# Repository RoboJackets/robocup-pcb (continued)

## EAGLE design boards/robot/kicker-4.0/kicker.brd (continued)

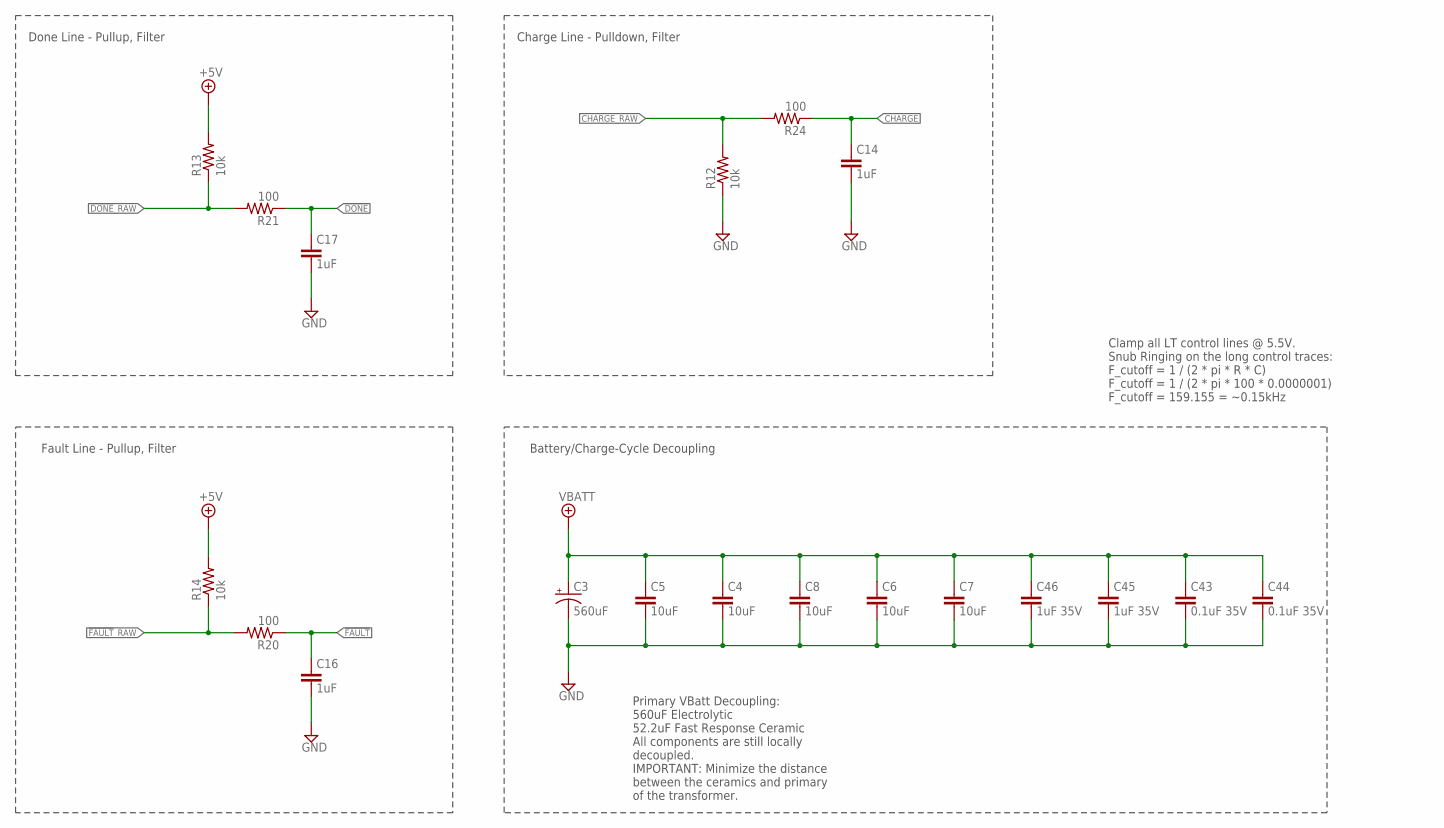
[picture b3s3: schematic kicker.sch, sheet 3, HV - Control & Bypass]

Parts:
C3: 560uF; E7,5-18
C4, C5, C6, C7, C8: 10uF; C1210
C14, C16, C17: 1uF; C0603
C43, C44: 0.1uF 35V; C0805
C45, C46: 1uF 35V; C0805
R12, R13, R14: 10k; R0603
R20, R21, R24: 100; R0603

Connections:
!DONE!: C17.1, R21.1; also elsewhere on the board
!DONE!_RAW: R13.1, R21.2; also elsewhere on the board
!FAULT!: C16.1, R20.1; also elsewhere on the board
!FAULT!_RAW: R14.1, R20.2; also elsewhere on the board
+5V: R13.2, R14.2; also elsewhere on the board
CHARGE: C14.1, R24.1; also elsewhere on the board
CHARGE_RAW: R12.2, R24.2; also elsewhere on the board
GND: C3.-, C4.2, C5.2, C6.2, C7.2, C8.2, C14.2, C16.2, C17.2, C43.2, C44.2, C45.2, C46.2, R12.1; also elsewhere on the board
VBATT: C3.+, C4.1, C5.1, C6.1, C7.1, C8.1, C43.1, C44.1, C45.1, C46.1; also elsewhere on the board

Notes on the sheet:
Done Line - Pullup, Filter
Fault Line - Pullup, Filter
Charge Line - Pulldown, Filter
Battery/Charge-Cycle Decoupling
Clamp all LT control lines @ 5.5V. Snub Ringing on the long control traces: F_cutoff = 1 / (2 * pi * R * C) F_cutoff = 1 / (2 * pi * 100 * 0.0000001) F_cutoff = 159.155 = ~0.15kHz
Primary VBatt Decoupling: 560uF Electrolytic 52.2uF Fast Response Ceramic All components are still locally decoupled. IMPORTANT: Minimize the distance between the ceramics and primary of the transformer.

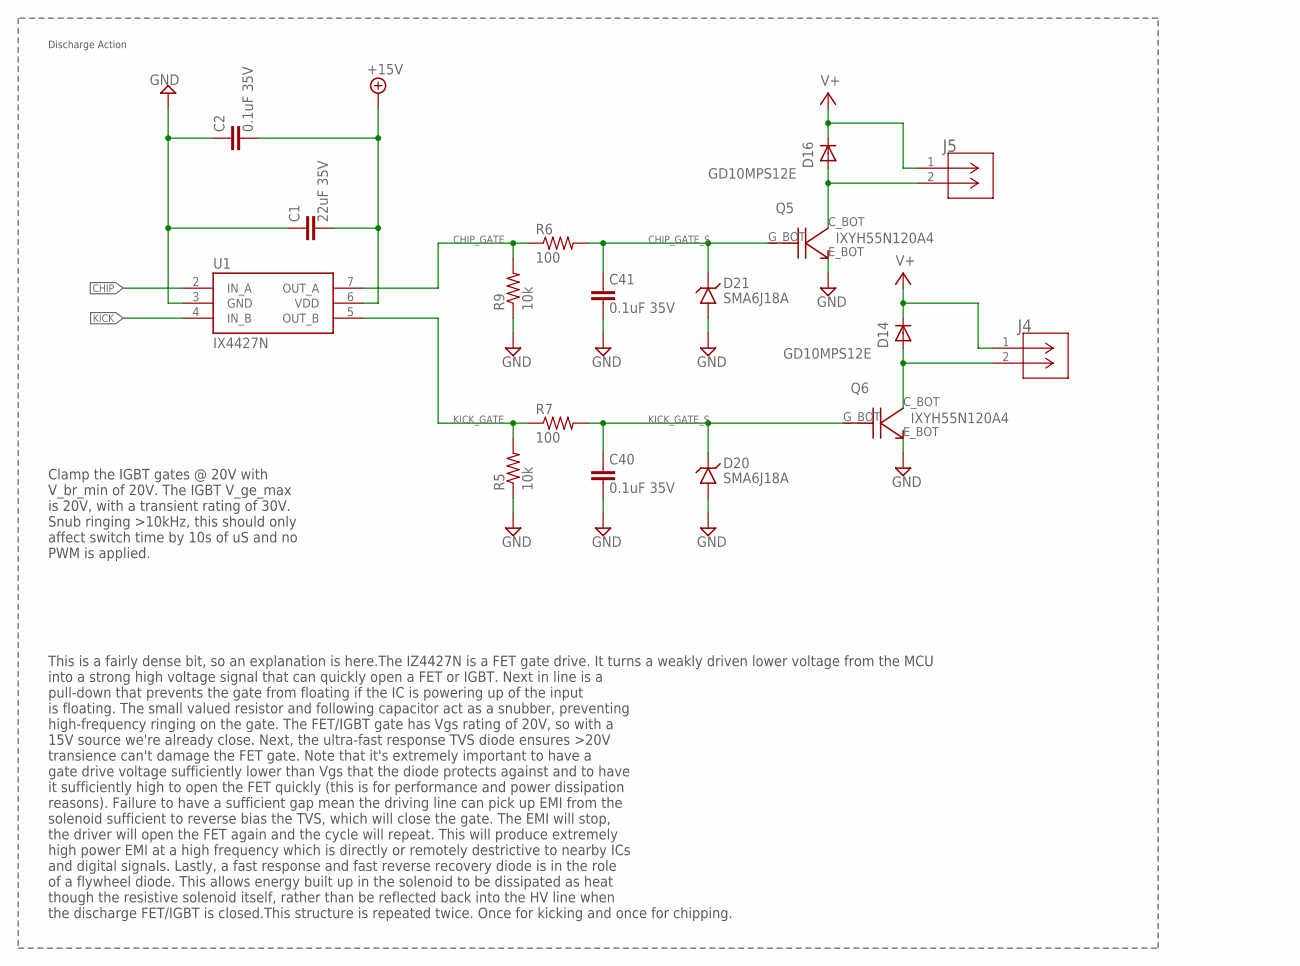
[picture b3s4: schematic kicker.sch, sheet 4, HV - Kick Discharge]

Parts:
C1: 22uF 35V; C0805
C2: 0.1uF 35V; C0805
C40, C41: 0.1uF 35V; C0603
D14, D16: GD10MPS12E; TO460P990X239-3
D20, D21: SMA6J18A; RESM5226X262
J4, J5: 436500202; CON_436500202_MOL
Q5, Q6: IXYH55N120A4; TO264
R5, R9: 10k; R0603
R6, R7: 100; R1206
U1: IX4427N; SOIC-8

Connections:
+15V: C1.2, C2.2, U1.6 (VDD); also elsewhere on the board
CHIP: U1.2 (IN_A); also elsewhere on the board
CHIPPER: D16.2 (A), J5.2, Q5.C_BOT (C)
CHIP_GATE: R6.1, R9.2, U1.7 (OUT_A)
CHIP_GATE_S: C41.1, D21.2 (C), Q5.G_BOT (G), R6.2
GND: C1.1, C2.1, C40.2, C41.2, D20.1 (A), D21.1 (A), Q5.E_BOT (E), Q6.E_BOT (E), R5.1, R9.1, U1.3 (GND); also elsewhere on the board
KICK: U1.4 (IN_B); also elsewhere on the board
KICKER: D14.2 (A), J4.2, Q6.C_BOT (C)
KICK_GATE: R5.2, R7.1, U1.5 (OUT_B)
KICK_GATE_S: C40.1, D20.2 (C), Q6.G_BOT (G), R7.2
V+: D14.3 (C), D16.3 (C), J4.1, J5.1; also elsewhere on the board

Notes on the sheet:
Discharge Action
Clamp the IGBT gates @ 20V with V_br_min of 20V. The IGBT V_ge_max is 20V, with a transient rating of 30V. Snub ringing >10kHz, this should only affect switch time by 10s of uS and no PWM is applied.
This is a fairly dense bit, so an explanation is here.The IZ4427N is a FET gate drive. It turns a weakly driven lower voltage from the MCU into a strong high voltage signal that can quickly open a FET or IGBT. Next in line is a pull-down that prevents the gate from floating if the IC is powering up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

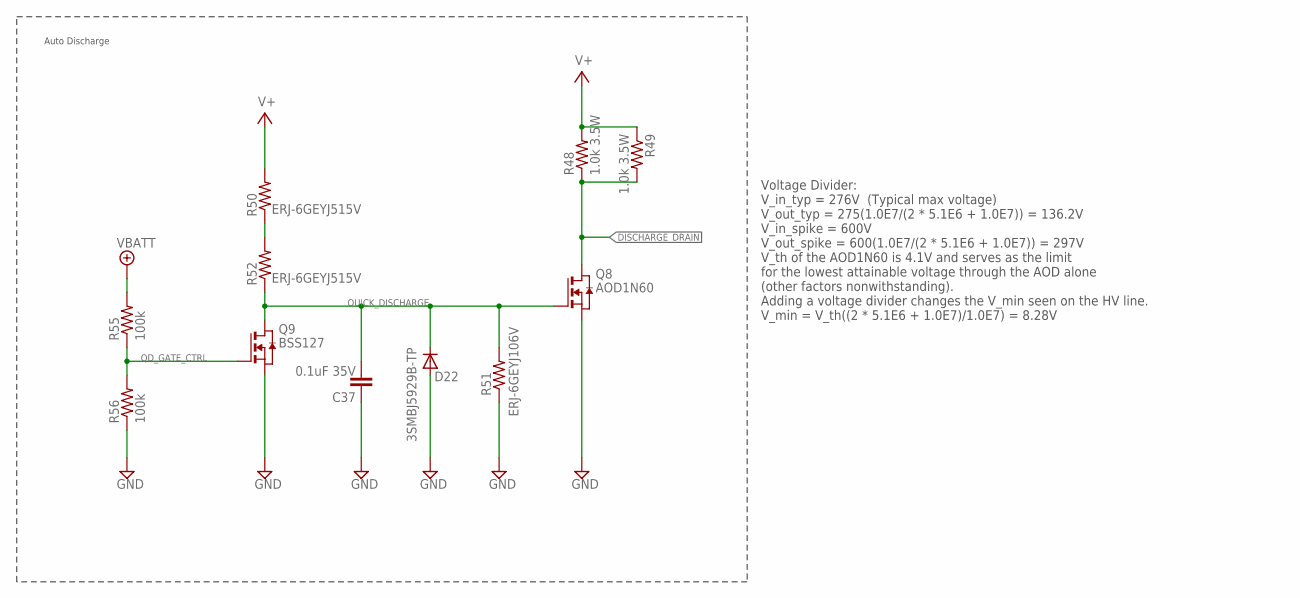
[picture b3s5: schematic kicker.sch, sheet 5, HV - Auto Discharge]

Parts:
C37: 0.1uF 35V; C0603
D22: 3SMBJ5929B-TP; DO214AA
Q8: AOD1N60; DPAK
Q9: BSS127; SOT-23-3
R48, R49: 1.0k 3.5W; TO508P1539X450-3; DIGIKEY PWR263S-35-1501F
R50, R52: ERJ-6GEYJ515V; R0805
R51: ERJ-6GEYJ106V; R0603
R55, R56: 100k; R0603

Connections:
DISCHARGE_DRAIN: Q8.4 (D), R48.1 (PIN1), R49.2 (PIN2); also elsewhere on the board
GND: C37.1, D22.A, Q8.3 (S), Q9.2 (S), R51.1, R56.1; also elsewhere on the board
QD_GATE_CTRL: Q9.1 (G), R55.1, R56.2
QD_PU_BR: R50.1, R52.2
QUICK_DISCHARGE: C37.2, D22.C, Q8.1 (G), Q9.3 (D), R51.2, R52.1
V+: R48.2 (PIN2), R49.1 (PIN1), R50.2; also elsewhere on the board
VBATT: R55.2; also elsewhere on the board

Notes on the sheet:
Auto Discharge
Voltage Divider: V_in_typ = 276V (Typical max voltage) V_out_typ = 275(1.0E7/(2 * 5.1E6 + 1.0E7)) = 136.2V V_in_spike = 600V V_out_spike = 600(1.0E7/(2 * 5.1E6 + 1.0E7)) = 297V V_th of the AOD1N60 is 4.1V and serves as the limit for the lowest attainable voltage through the AOD alone (other factors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

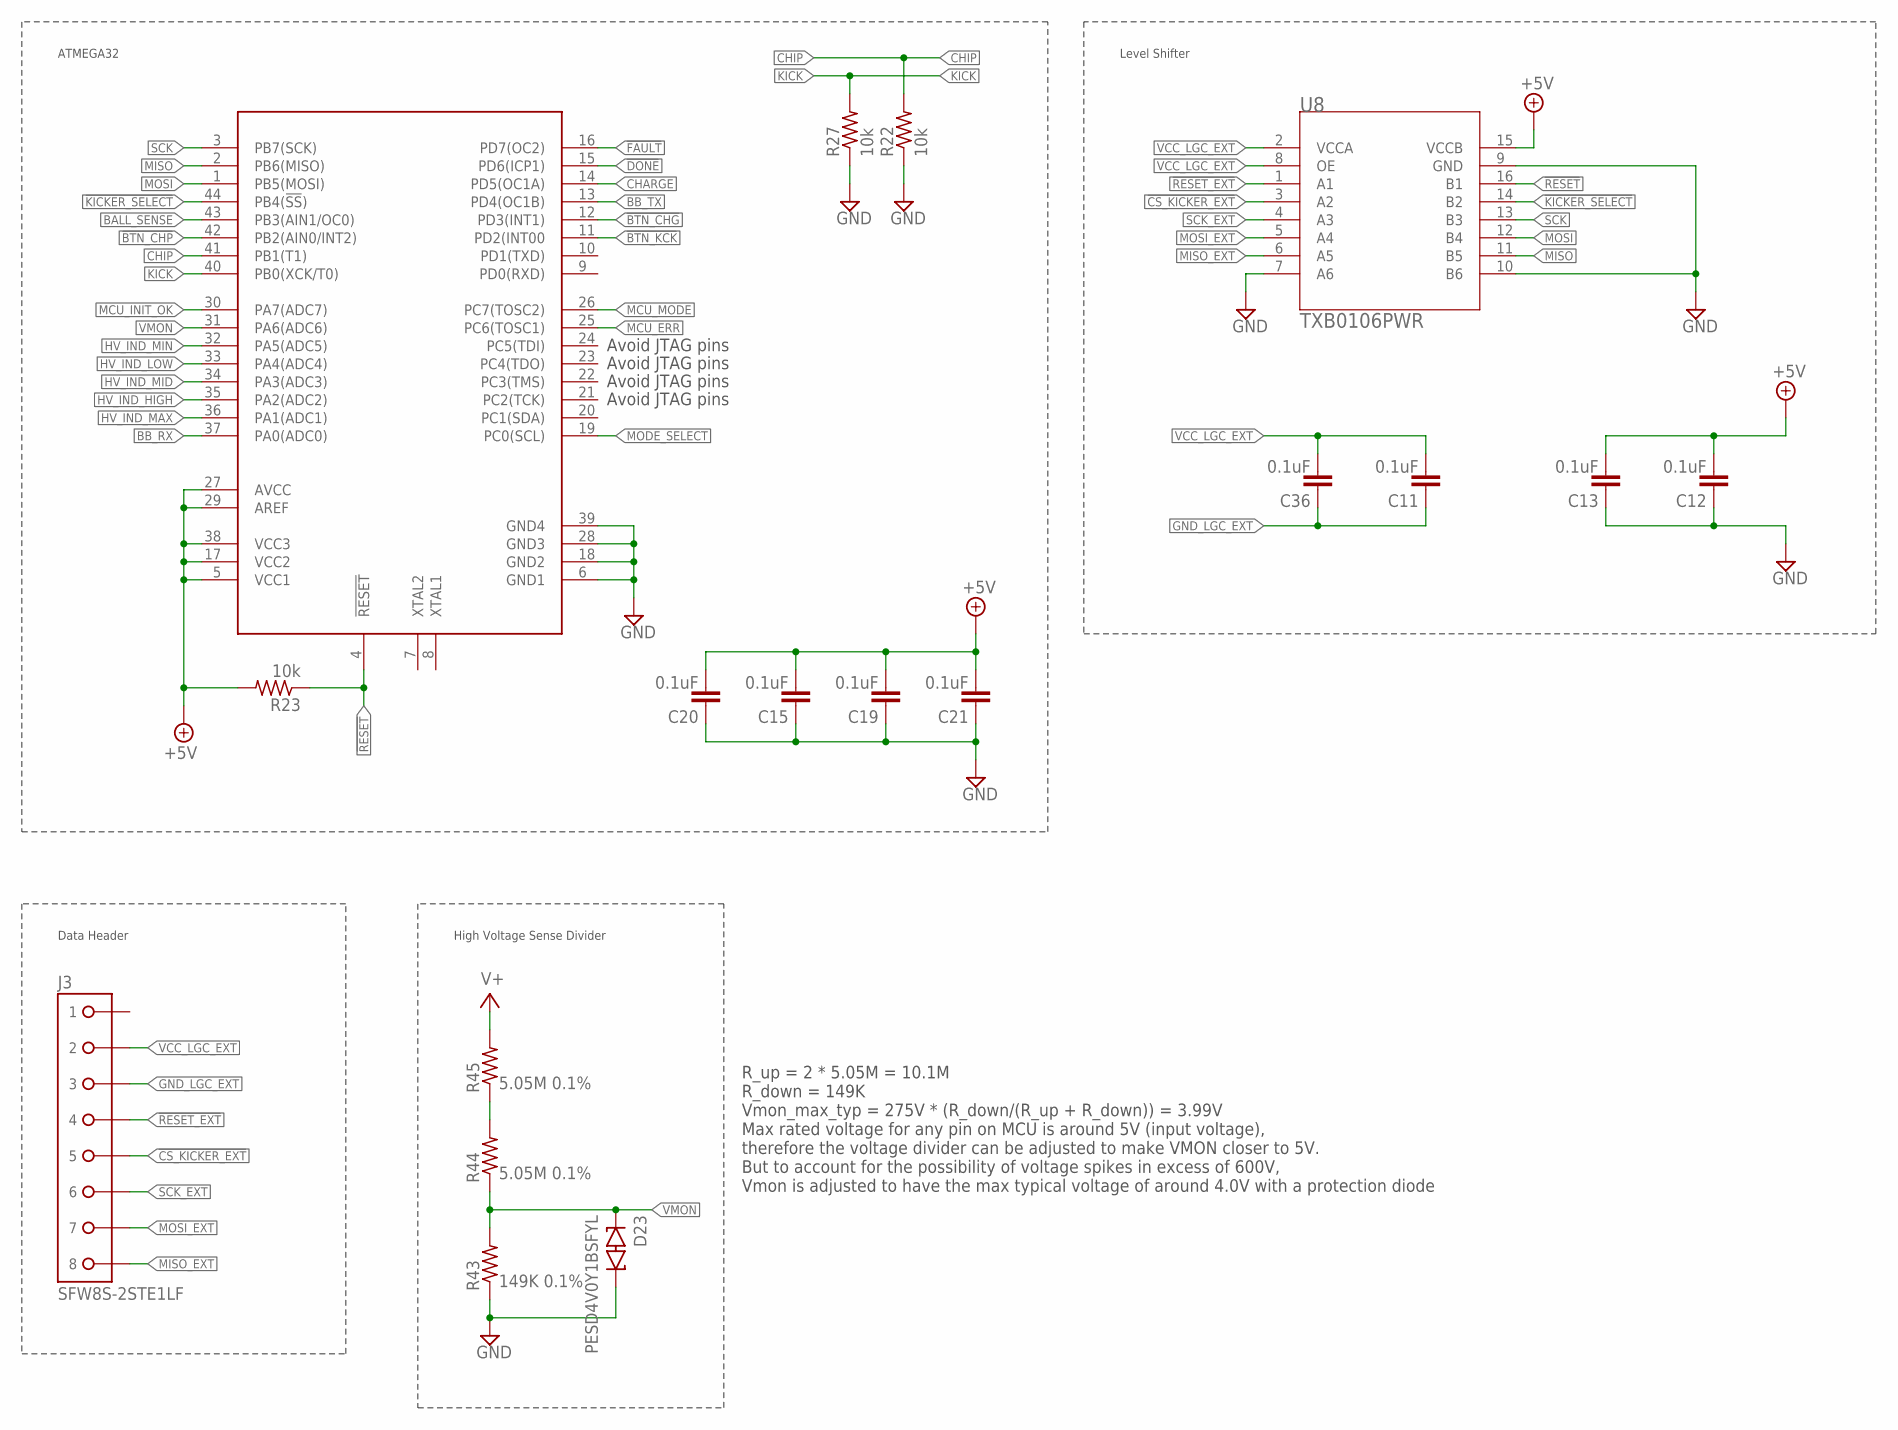
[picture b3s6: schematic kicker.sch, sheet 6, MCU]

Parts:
C11, C12, C13, C15, C19, C20, C21, C36: 0.1uF; C0603
D23: PESD4V0Y1BSFYL; DSN0603-2
J3: SFW8S-2STE1LF; CON8_1X8_UB_SFW_JAE
R22, R23, R27: 10k; R0603
R43: 149K 0.1%; R0603
R44, R45: 5.05M 0.1%; R0805
U5: AT32ATQFP44; QFP80P1200X1200X120-44
U8: TXB0106PWR; PW16

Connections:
!BTN_CHG: U5.12 (PD3(INT1)); also elsewhere on the board
!BTN_CHP: U5.42 (PB2(AIN0/INT2)); also elsewhere on the board
!BTN_KCK: U5.11 (PD2(INT00); also elsewhere on the board
!CS_KICKER_EXT: J3.5, U8.3 (A2)
!DONE!: U5.15 (PD6(ICP1)); also elsewhere on the board
!FAULT!: U5.16 (PD7(OC2)); also elsewhere on the board
!KICKER_SELECT: U5.44 (PB4(!SS!)), U8.14 (B2)
!RESET: R23.1, U5.4 (!RESET!), U8.16 (B1)
!RESET_EXT: J3.4, U8.1 (A1)
+5V: C12.2, C13.2, C15.2, C19.2, C20.2, C21.2, R23.2, U5.5 (VCC1), U5.17 (VCC2), U5.27 (AVCC), U5.29 (AREF), U5.38 (VCC3), U8.15 (VCCB); also elsewhere on the board
BALL_SENSE: U5.43 (PB3(AIN1/OC0)); also elsewhere on the board
BB_RX: U5.37 (PA0(ADC0)); also elsewhere on the board
BB_TX: U5.13 (PD4(OC1B)); also elsewhere on the board
CHARGE: U5.14 (PD5(OC1A)); also elsewhere on the board
CHIP: R22.2, U5.41 (PB1(T1)); also elsewhere on the board
GND: C12.1, C13.1, C15.1, C19.1, C20.1, C21.1, D23.C2, R22.1, R27.1, R43.1, U5.6 (GND1), U5.18 (GND2), U5.28 (GND3), U5.39 (GND4), U8.7 (A6), U8.9 (GND), U8.10 (B6); also elsewhere on the board
GND_LGC_EXT: C11.1, C36.1, J3.3
HV_IND_HIGH: U5.35 (PA2(ADC2)); also elsewhere on the board
HV_IND_LOW: U5.33 (PA4(ADC4)); also elsewhere on the board
HV_IND_MAX: U5.36 (PA1(ADC1)); also elsewhere on the board
HV_IND_MID: U5.34 (PA3(ADC3)); also elsewhere on the board
HV_IND_MIN: U5.32 (PA5(ADC5)); also elsewhere on the board
HV_SENSE_DIV_BR: R44.2, R45.1
KICK: R27.2, U5.40 (PB0(XCK/T0)); also elsewhere on the board
MCU_ERR: U5.25 (PC6(TOSC1)); also elsewhere on the board
MCU_INIT_OK: U5.30 (PA7(ADC7)); also elsewhere on the board
MCU_MODE: U5.26 (PC7(TOSC2)); also elsewhere on the board
MISO: U5.2 (PB6(MISO)), U8.11 (B5)
MISO_EXT: J3.8, U8.6 (A5)
MODE_SELECT: U5.19 (PC0(SCL)); also elsewhere on the board
MOSI: U5.1 (PB5(MOSI)), U8.12 (B4)
MOSI_EXT: J3.7, U8.5 (A4)
SCK: U5.3 (PB7(SCK)), U8.13 (B3)
SCK_EXT: J3.6, U8.4 (A3)
V+: R45.2; also elsewhere on the board
VCC_LGC_EXT: C11.2, C36.2, J3.2, U8.2 (VCCA), U8.8 (OE)
VMON: D23.C1, R43.2, R44.1, U5.31 (PA6(ADC6))

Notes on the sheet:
ATMEGA32
Data Header
High Voltage Sense Divider
Avoid JTAG pins
R_up = 2 * 5.05M = 10.1M R_down = 149K Vmon_max_typ = 275V * (R_down/(R_up + R_down)) = 3.99V Max rated voltage for any pin on MCU is around 5V (input voltage), therefore the voltage divider can be adjusted to make VMON closer to 5V. But to account for the possibility of voltage spikes in excess of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
Level Shifter

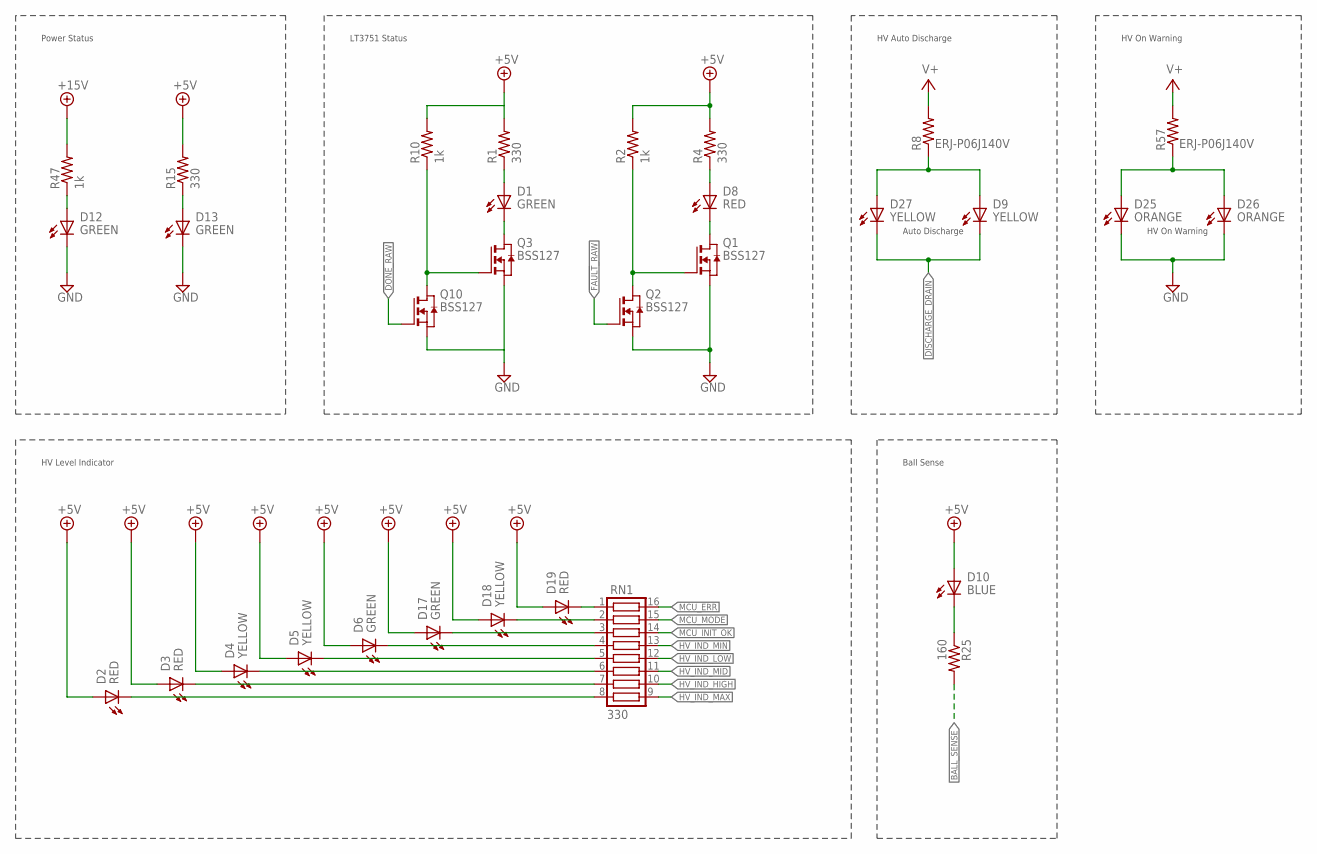
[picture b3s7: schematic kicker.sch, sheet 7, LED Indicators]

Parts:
D1, D6, D12, D13, D17: GREEN; CHIP-LED0603
D2, D3, D8, D19: RED; CHIP-LED0603
D4, D5, D9, D18, D27: YELLOW; CHIP-LED0603
D10: BLUE; CHIP-LED0603
D25, D26: ORANGE; CHIP-LED0603; MPN LTST-C191KFKT; DIGIKEY 160-1445-1-ND
Q1, Q2, Q3, Q10: BSS127; SOT-23-3
R1, R4, R15: 330; R0603
R2, R10, R47: 1k; R0603
R8, R57: ERJ-P06J140V; R0805
R25: 160; R0603
RN1: 330; RA-8_2506

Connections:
15V_PWR_BR: D12.A, R47.1
!DONE!_RAW: Q10.1 (G); also elsewhere on the board
!FAULT!_RAW: Q2.1 (G); also elsewhere on the board
+5V: D2.A, D3.A, D4.A, D5.A, D6.A, D10.A, D17.A, D18.A, D19.A, R1.2, R2.2, R4.2, R10.2, R15.2; also elsewhere on the board
+15V: R47.2; also elsewhere on the board
BALL_SENSE: R25.2; also elsewhere on the board
BALL_SENSE_CL: D10.C (K), R25.1
DISCHARGE_DRAIN: D9.C (K), D27.C (K); also elsewhere on the board
FAULT_INV_BR: Q1.1 (G), Q2.3 (D), R2.1
FAULT_INV_BR1: Q3.1 (G), Q10.3 (D), R10.1
GND: D12.C (K), D13.C (K), D25.C (K), D26.C (K), Q1.2 (S), Q2.2 (S), Q3.2 (S); also elsewhere on the board
GND1: Q10.2 (S)
HV_IND_HIGH: RN1.10; also elsewhere on the board
HV_IND_HIGH_CL: D3.C (K), RN1.7
HV_IND_LOW: RN1.12; also elsewhere on the board
HV_IND_LOW_CL: D5.C (K), RN1.5
HV_IND_MAX: RN1.9; also elsewhere on the board
HV_IND_MAX_CL: D2.C (K), RN1.8
HV_IND_MID: RN1.11; also elsewhere on the board
HV_IND_MID_CL: D4.C (K), RN1.6
HV_IND_MIN: RN1.13; also elsewhere on the board
HV_IND_MIN_CL: D6.C (K), RN1.4
MCU_ERR: RN1.16; also elsewhere on the board
MCU_ERR_CL: D19.C (K), RN1.1
MCU_INIT_OK: RN1.14; also elsewhere on the board
MCU_INIT_OK_CL: D17.C (K), RN1.3
MCU_MODE: RN1.15; also elsewhere on the board
MCU_MODE_CL: D18.C (K), RN1.2
unnamed: D25.A, D26.A, R57.1
unnamed: D1.A, R1.1
unnamed: D13.A, R15.1
unnamed: D8.A, R4.1
unnamed: D8.C (K), Q1.3 (D)
unnamed: D9.A, D27.A, R8.1
unnamed: D1.C (K), Q3.3 (D)
V+: R8.2, R57.2; also elsewhere on the board

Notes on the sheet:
Power Status
LT3751 Status
Auto Discharge
HV Auto Discharge
HV Level Indicator
Ball Sense
HV On Warning

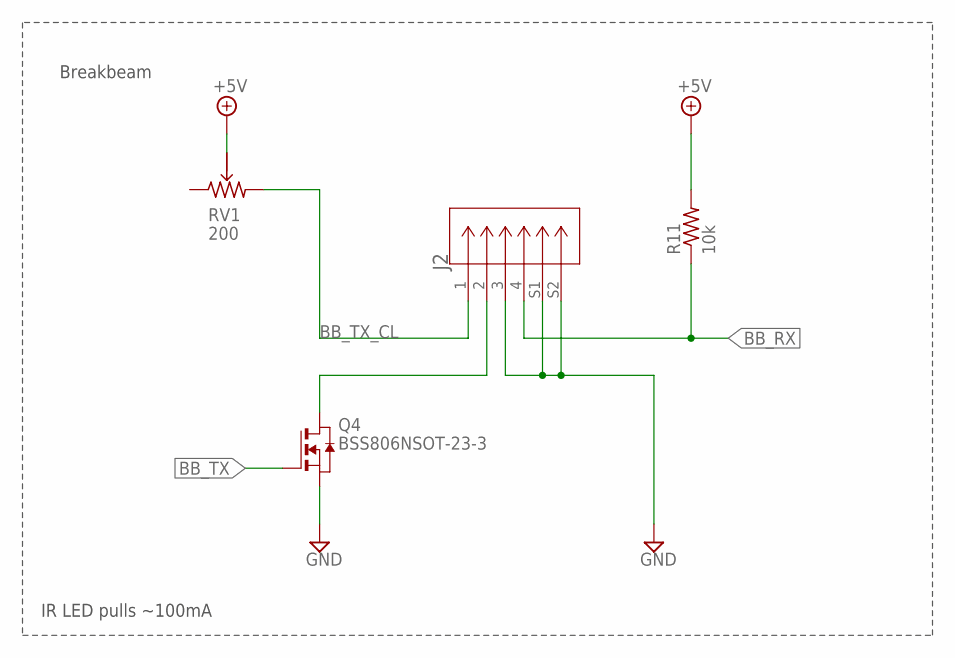
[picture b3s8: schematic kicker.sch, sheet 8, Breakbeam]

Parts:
J2: 430450411; CON_430450411_MOL
Q4: BSS806NSOT-23-3; SOT95P240X110-3
R11: 10k; R0603
RV1: 200; 3214J

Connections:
+5V: R11.2, RV1.P$2 (PIN2); also elsewhere on the board
BB_RX: J2.4, R11.1; also elsewhere on the board
BB_TX: Q4.1 (G); also elsewhere on the board
BB_TX_CL: J2.1, RV1.P$3 (PIN3)
GND: J2.3, J2.S1, J2.S2, Q4.2 (S); also elsewhere on the board
unnamed: J2.2, Q4.3 (D)

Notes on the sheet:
Breakbeam
IR LED pulls ~100mA

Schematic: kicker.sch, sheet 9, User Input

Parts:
C22, C26, C28: 0.1uF; C0603
R16, R28, R29, R34: 10k; R0603
S2, S3, S4: KSS32
S6: TT11EGPC1

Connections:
!BTN_CHG: C28.1, R34.1, S4.2; also elsewhere on the board
!BTN_CHP: C22.1, R28.1, S2.2; also elsewhere on the board
!BTN_KCK: C26.1, R29.1, S3.2; also elsewhere on the board
+5V: R28.2, R29.2, R34.2, S6.1 (A); also elsewhere on the board
GND: C22.2, C26.2, C28.2, S2.1, S3.1, S4.1, S6.2 (B); also elsewhere on the board
MODE_SELECT: R16.2; also elsewhere on the board
unnamed: R16.1, S6.3 (COMMON)

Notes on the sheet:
Debug Mode Select
Chip/Kick Switch

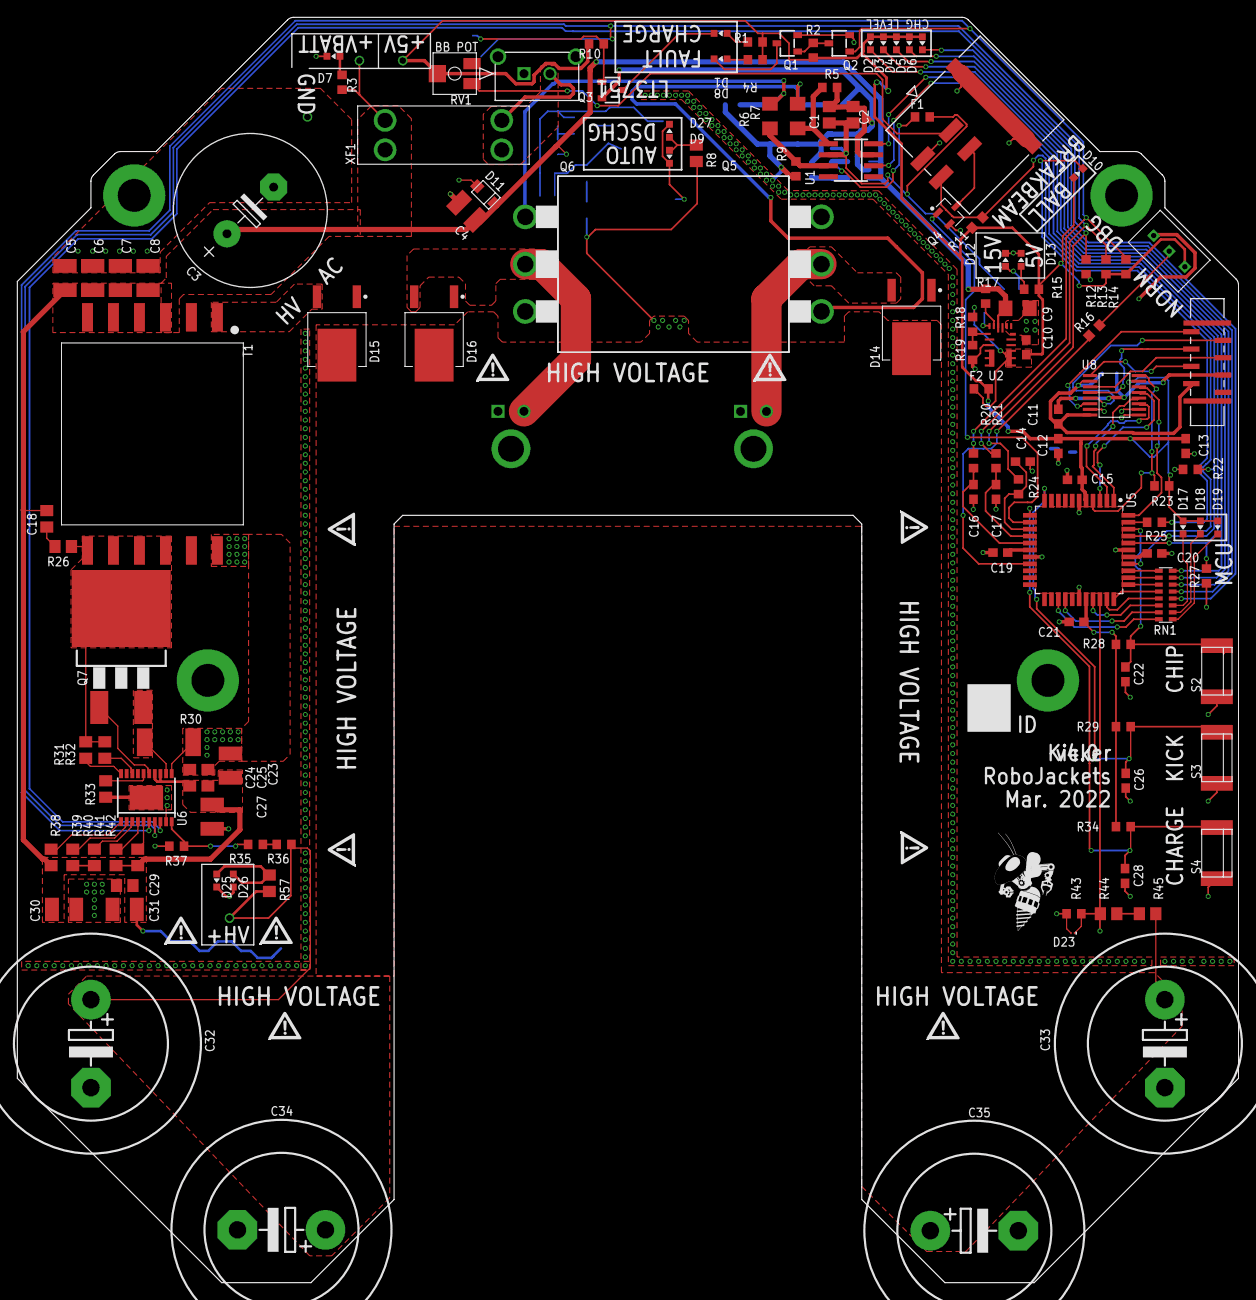
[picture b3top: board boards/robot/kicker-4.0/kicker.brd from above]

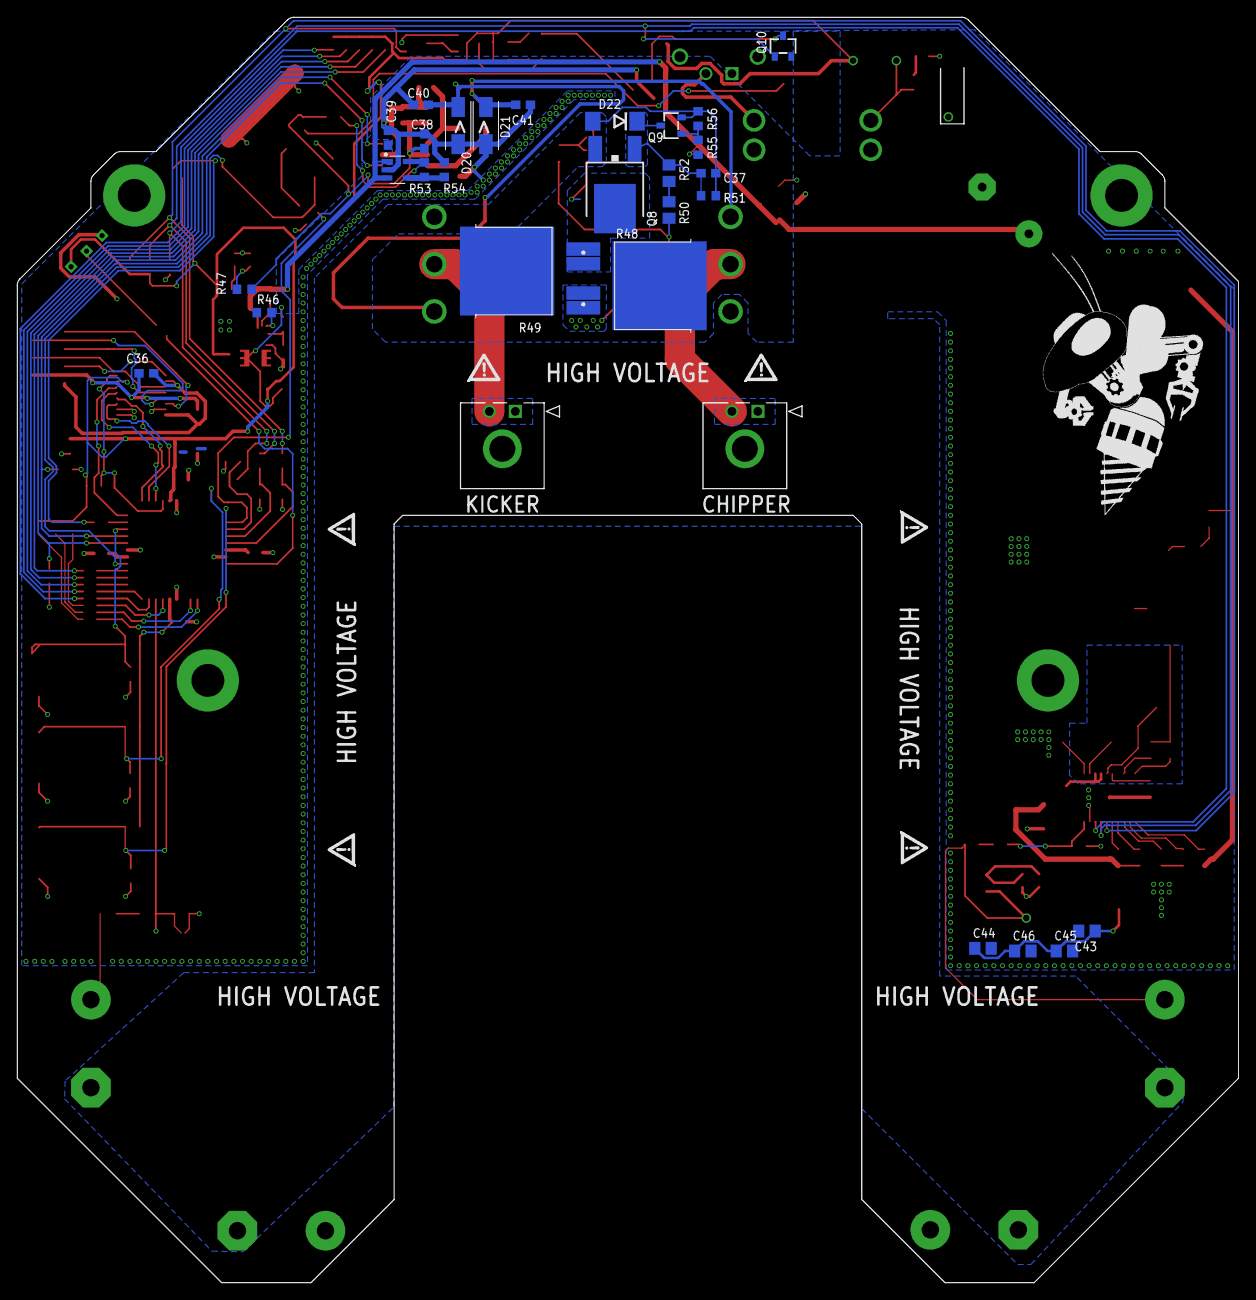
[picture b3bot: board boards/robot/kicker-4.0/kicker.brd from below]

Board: 2 copper layers, 141.0 x 146.1 mm, 177 parts (37 on the bottom side), 97 nets.

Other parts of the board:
U$1, U$2, U$3, U$4, U$7, U$8, U$9, U$10, U$11, U$12, U$13, U$14, U$15, U$16, U$17, U$18: WARNING2
U$5: ROBOBUZZ_0.6X
U$6: ROBOBUZZ_1.4X

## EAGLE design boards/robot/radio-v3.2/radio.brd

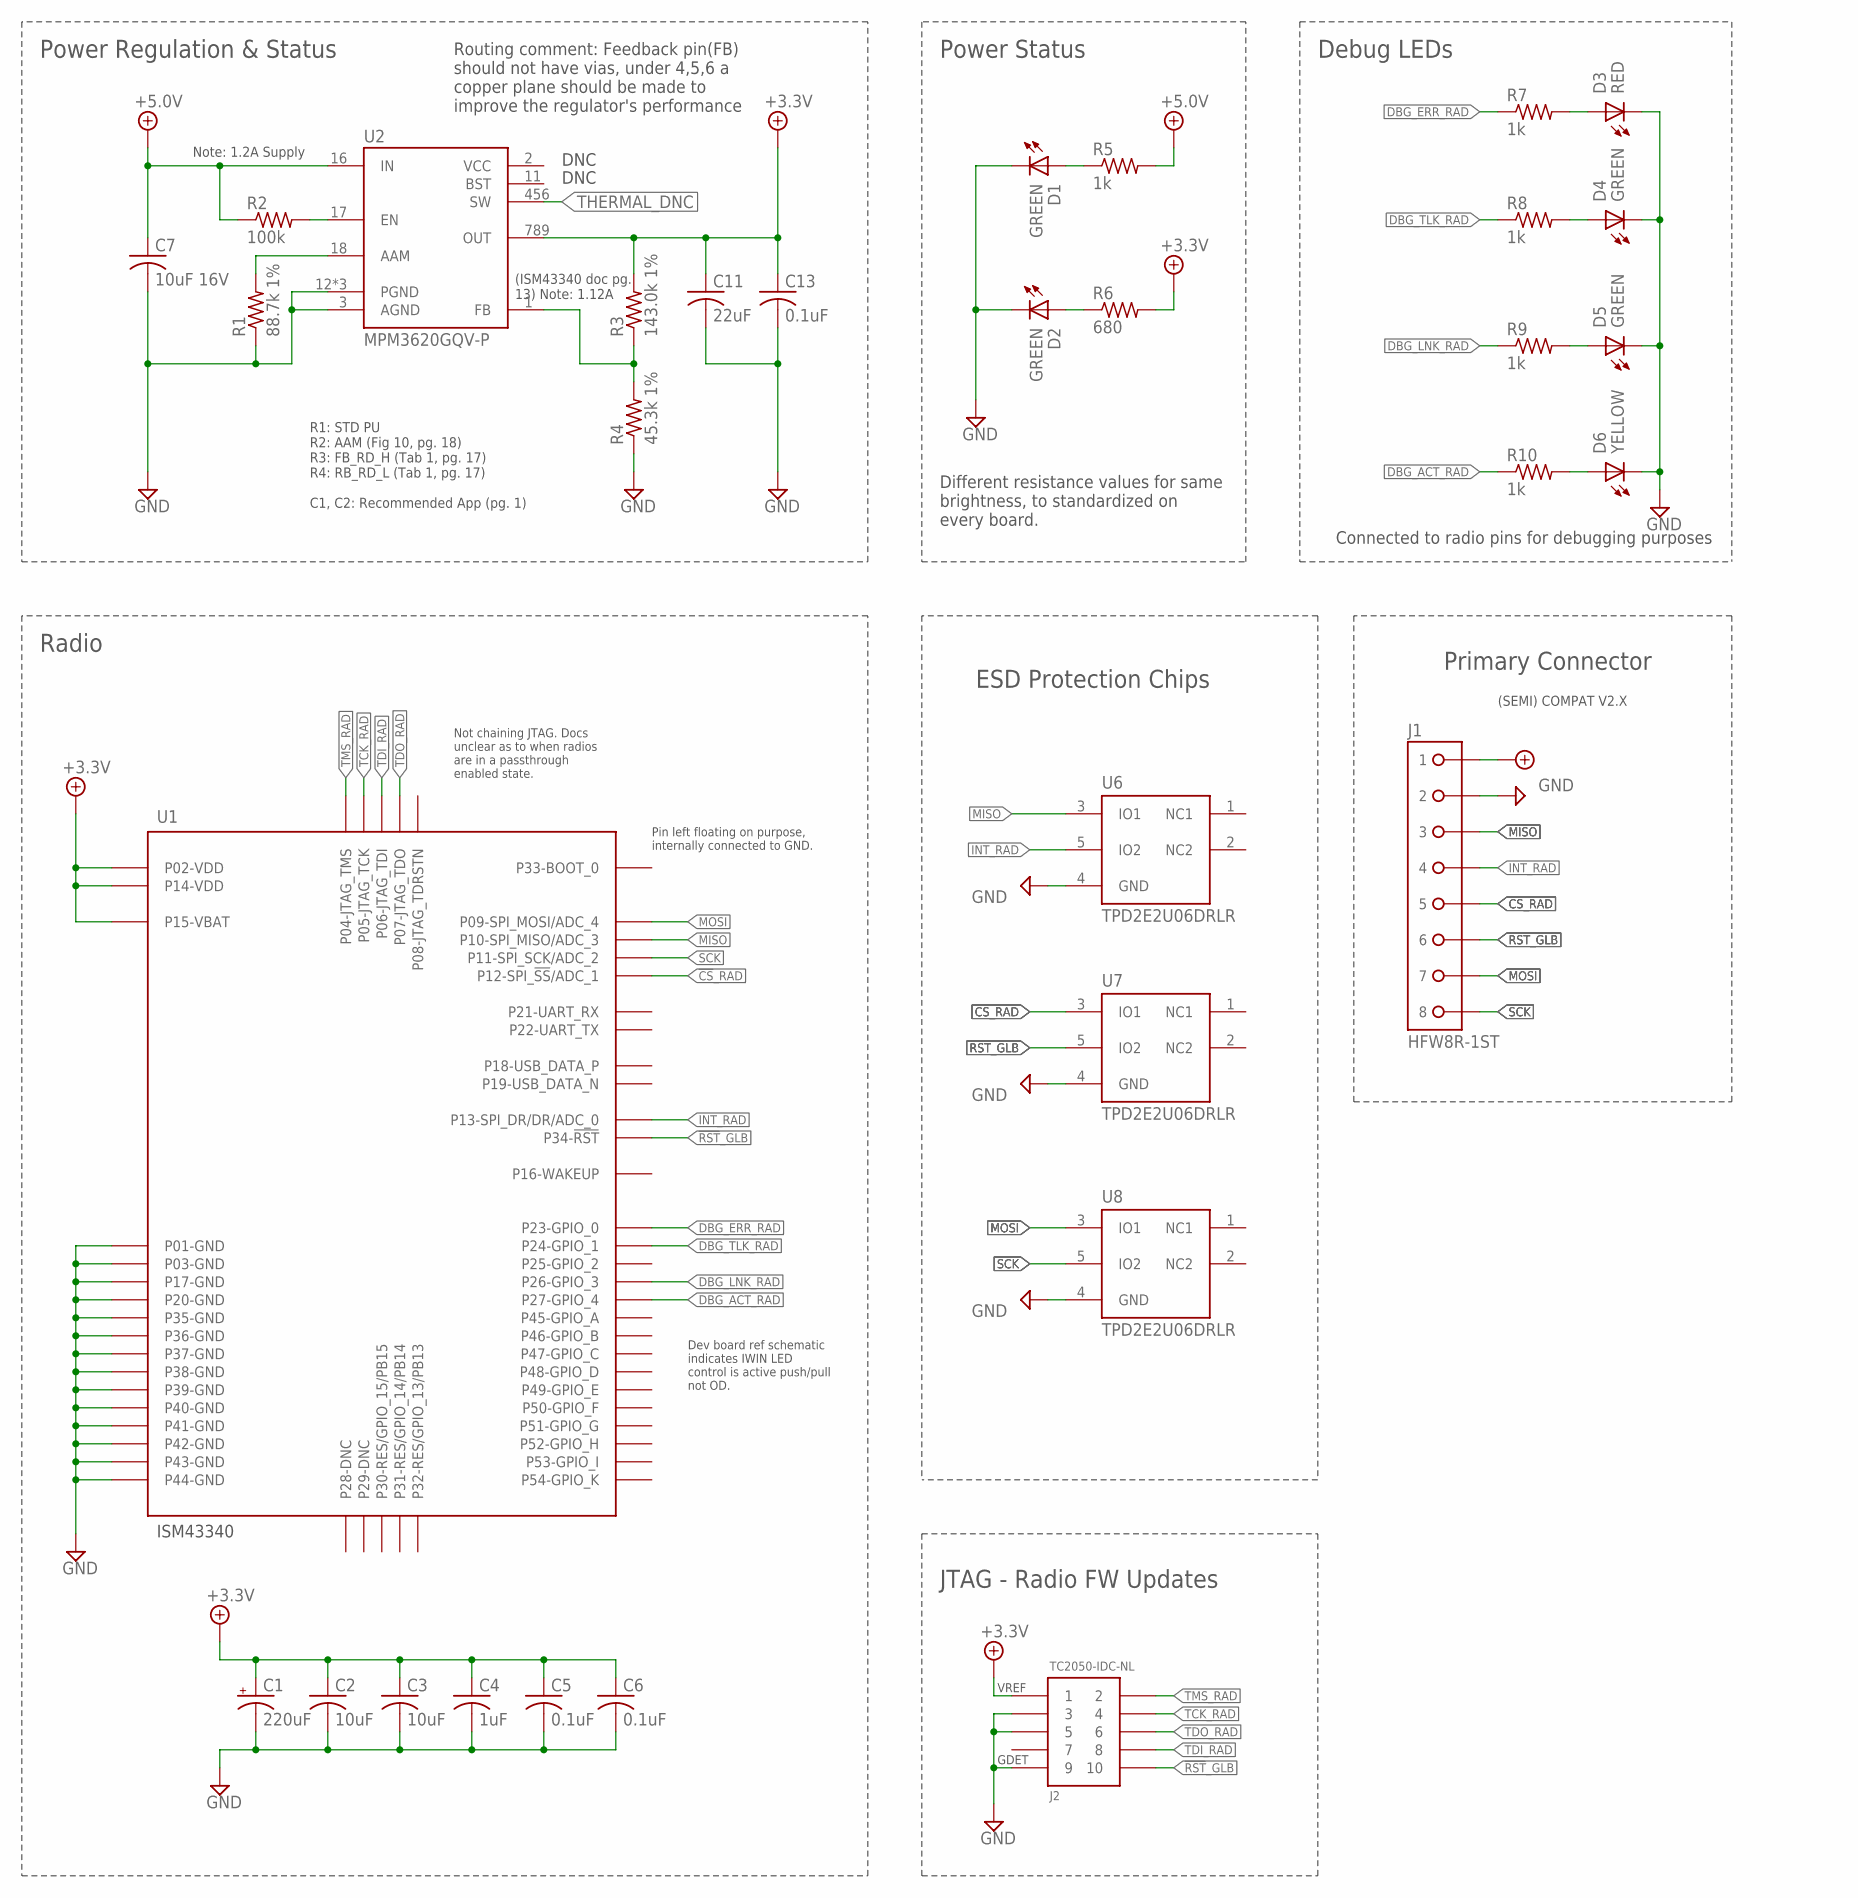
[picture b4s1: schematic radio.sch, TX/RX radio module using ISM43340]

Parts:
C1: 220uF; ECA-0JM221-HGT_HORIZ
C2, C3: 10uF; C0805
C4: 1uF; C0603
C5, C6, C13: 0.1uF; C0603
C7: 10uF 16V; C1210
C11: 22uF; C1210
D1, D2, D4, D5: GREEN; CHIP-LED0603
D3: RED; CHIP-LED0603
D6: YELLOW; CHIP-LED0603
J1: HFW8R-1ST
J2: TC2050-IDC-NL
R1: 88.7k 1%; R0603
R2: 100k; R0603
R3: 143.0k 1%; R0603
R4: 45.3k 1%; R0603
R5, R7, R8, R9, R10: 1k; R0603
R6: 680; R0603
U1: ISM43340
U2: MPM3620GQV-P
U6, U7, U8: TPD2E2U06DRLR; SOT-553

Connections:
3V3_PWR_IND: D2.A, R6.1
5V_PWR_IND: D1.A, R5.1
!CS!_RAD: J1.5, U1.P$12 (P12-SPI_!SS!/ADC_1), U7.3 (IO1)
!RST!_GLB: J1.6, J2.10, U1.P$34 (P34-!RST!), U7.5 (IO2)
+3.3V: C1.P$1 (+), C2.1, C3.1, C4.1, C5.1, C6.1, C11.1, C13.1, J2.1, R3.2, R6.2, U1.P$2 (P02-VDD), U1.P$14 (P14-VDD), U1.P$15 (P15-VBAT), U2.789 (OUT)
+5.0V: C7.1, J1.1, R2.1, R5.2, U2.16 (IN)
AAM: R1.2, U2.18 (AAM)
DBG_ACT_RAD: R10.1, U1.P$27 (P27-GPIO_4)
DBG_ERR: D3.A, R7.2
DBG_ERR_RAD: R7.1, U1.P$23 (P23-GPIO_0)
DBG_LNK_RAD: R9.1, U1.P$26 (P26-GPIO_3)
DBG_TLK_RAD: R8.1, U1.P$24 (P24-GPIO_1)
DGB_ACT: D6.A, R10.2
DGB_LNK: D5.A, R9.2
EN: R2.2, U2.17 (EN)
FB: R3.1, R4.2, U2.1 (FB)
GND: C1.P$2 (-), C2.2, C3.2, C4.2, C5.2, C6.2, C7.2, C11.2, C13.2, D1.C (K), D2.C (K), D3.C (K), D4.C (K), D5.C (K), D6.C (K), J1.2, J2.3, J2.5, J2.9, R1.1, R4.1, U1.P$1 (P01-GND), U1.P$3 (P03-GND), U1.P$17 (P17-GND), U1.P$20 (P20-GND), U1.P$35 (P35-GND), U1.P$36 (P36-GND), U1.P$37 (P37-GND), U1.P$38 (P38-GND), U1.P$39 (P39-GND), U1.P$40 (P40-GND), U1.P$41 (P41-GND), U1.P$42 (P42-GND), U1.P$43 (P43-GND), U1.P$44 (P44-GND), U2.3 (AGND), U2.12 (PGND), U2.13 (PGND), U2.14 (PGND), U6.4 (GND), U7.4 (GND), U8.4 (GND)
INT_RAD: J1.4, U1.P$13 (P13-SPI_DR/DR/ADC_0), U6.5 (IO2)
MISO: J1.3, U1.P$10 (P10-SPI_MISO/ADC_3), U6.3 (IO1)
MOSI: J1.7, U1.P$9 (P09-SPI_MOSI/ADC_4), U8.3 (IO1)
SCK: J1.8, U1.P$11 (P11-SPI_SCK/ADC_2), U8.5 (IO2)
TCK_RAD: J2.4, U1.P$5 (P05-JTAG_TCK)
TDI_RAD: J2.8, U1.P$6 (P06-JTAG_TDI)
TDO_RAD: J2.6, U1.P$7 (P07-JTAG_TDO)
THERMAL_DNC: U2.456 (SW)
TLK: D4.A, R8.2
TMS_RAD: J2.2, U1.P$4 (P04-JTAG_TMS)

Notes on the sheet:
DNC
Primary Connector
Power Regulation & Status
Power Status
Note: 1.2A Supply
(ISM43340 doc pg. 13) Note: 1.12A
R1: STD PU R2: AAM (Fig 10, pg. 18) R3: FB_RD_H (Tab 1, pg. 17) R4: RB_RD_L (Tab 1, pg. 17) C1, C2: Recommended App (pg. 1)
Radio
Debug LEDs
VREF
GDET
JTAG - Radio FW Updates
Dev board ref schematic indicates IWIN LED control is active push/pull not OD.
Not chaining JTAG. Docs unclear as to when radios are in a passthrough enabled state.
(SEMI) COMPAT V2.X
ESD Protection Chips
Pin left floating on purpose, internally connected to GND.
Routing comment: Feedback pin(FB) should not have vias, under 4,5,6 a copper plane should be made to improve the regulator's performance
Connected to radio pins for debugging purposes
Different resistance values for same brightness, to standardized on every board.
